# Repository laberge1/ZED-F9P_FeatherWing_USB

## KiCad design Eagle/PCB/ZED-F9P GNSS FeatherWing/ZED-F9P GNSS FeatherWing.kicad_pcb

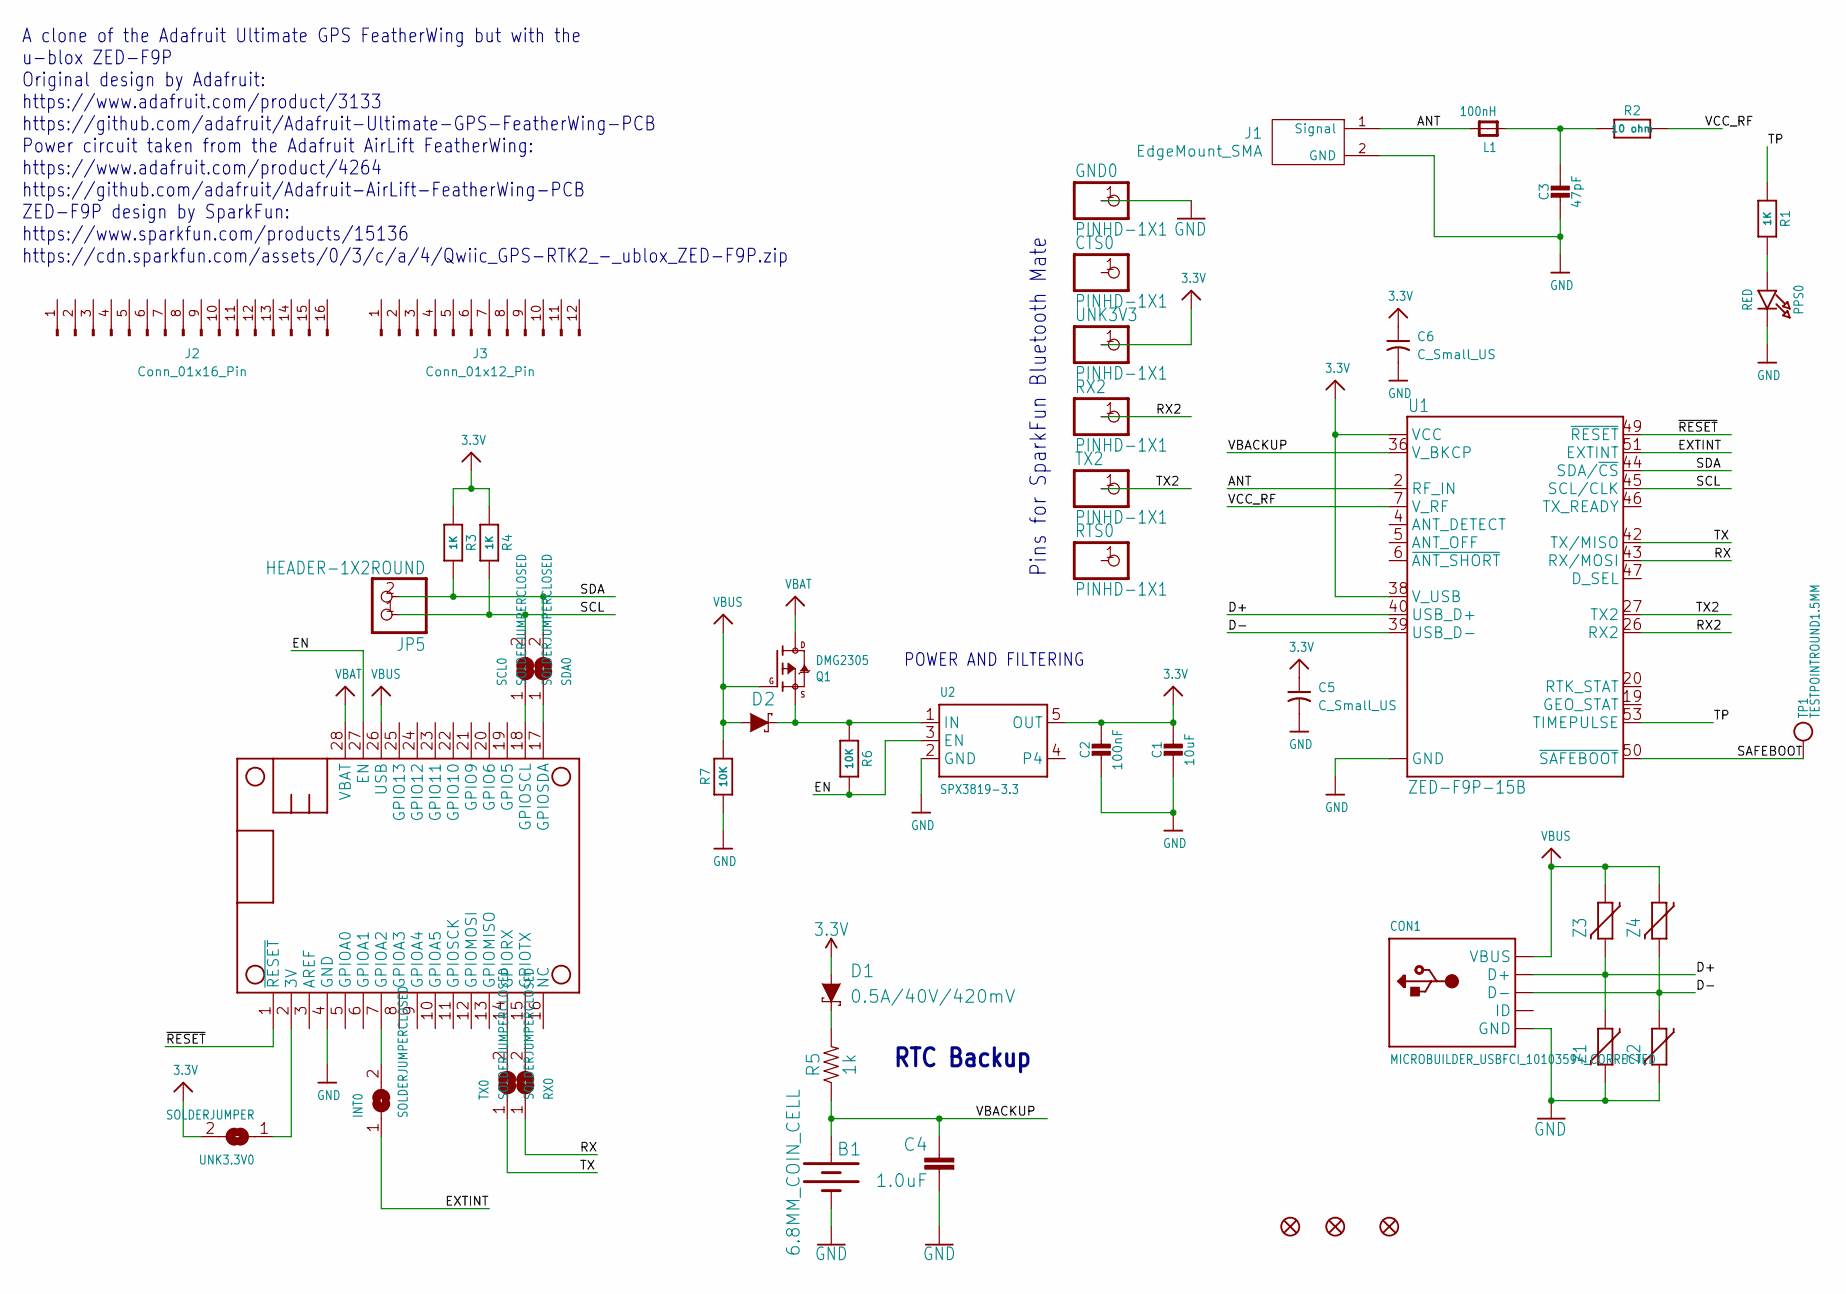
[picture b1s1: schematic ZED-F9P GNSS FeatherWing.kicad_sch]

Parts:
B1: 6.8MM_COIN_CELL; BATTCON-6.8MM; Digikey PN 728-1057-ND
C1: 10uF; 0805-NO; Voltage 6.3V; Digikey PN 1276-1298-1-ND
C2: 100nF; 0805-NO; Voltage 25V; Digikey PN 1276-2442-1-ND
C3: 47pF; C_0402_1005Metric; Digikey PN 490-14446-1-ND
C4: 1.0uF; 0603; Voltage 10V; Digikey PN 1276-1945-1-ND
C5, C6: C_Small_US; C_0402_1005Metric; Digikey PN 1276-1043-1-ND
CON1: MICROBUILDER_USBFCI_10103594_CORRECTED; MICROBUILDER_FCI_10103594_CORRECTED; Digikey PN 609-4050-1-ND
CTS0: PINHD-1X1; 1X01
D1, D2: 0.5A/40V/420mV; SOD-323; Digikey PN 1801-BAT201M3RRGCT-ND
FID1, FID2, FID3: FIDUCIAL""; Fiducial_0.5mm_Mask1mm
GND0: PINHD-1X1; 1X01
INT0: SOLDERJUMPERCLOSED; SolderJumper-2_P1.3mm_Bridged_RoundedPad1.0x1.5mm
J1: EdgeMount_SMA; SMA_Molex_0732512120; Digikey PN WM5536-ND
J2: Conn_01x16_Pin; Digikey PN 2223-SSK01-MPH-254-A16-ND
J3: Conn_01x12_Pin; Digikey PN 2223-SSK01-MPH-254-A12-ND
JP5: HEADER-1X2ROUND; 1X02_ROUND
L1: 100nH; L_0603_1608Metric; Digikey PN 490-15766-1-ND
MS1: MICROBUILDER_FEATHERWINGMICROBUILDER_FEATHERWING_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; MICROBUILDER_FEATHERWING_HOLES
PPS0: RED; CHIPLED_0805_NOOUTLINE; Digikey PN 732-4984-1-ND
Q1: DMG2305; SOT23-R; Digikey PN FDN340PCT-ND
R1, R3, R4: 1K; 0603-NO; Digikey PN 13-RT0603FRE131KLCT-ND
R2: 10 ohm; R_0402_1005Metric; Digikey PN CR0402-JW-100GLFCT-ND
R5: 1k; 0603; Digikey PN 13-RT0603FRE131KLCT-ND
R6, R7: 10K; 0603-NO; Digikey PN RNCP0603FTD10K0CT-ND
RTS0: PINHD-1X1; 1X01
RX0: SOLDERJUMPERCLOSED; SolderJumper-2_P1.3mm_Bridged_RoundedPad1.0x1.5mm
RX2: PINHD-1X1; 1X01
SCL0: SOLDERJUMPERCLOSED; SolderJumper-2_P1.3mm_Bridged_RoundedPad1.0x1.5mm
SDA0: SOLDERJUMPERCLOSED; SolderJumper-2_P1.3mm_Bridged_RoundedPad1.0x1.5mm
TP1: TESTPOINTROUND1.5MM; TESTPOINT_ROUND_1.5MM
TX0: SOLDERJUMPERCLOSED; SolderJumper-2_P1.3mm_Bridged_RoundedPad1.0x1.5mm
TX2: PINHD-1X1; 1X01
U1: ZED-F9P-15B; ZED-F9P_ZED-F9P; Digikey PN 672-ZED-F9P-15BCT-ND
U2: SPX3819-3.3; SOT23-5; Digikey PN 1016-1873-1-ND
UNK3.3V0: SOLDERJUMPER; SolderJumper-2_P1.3mm_Open_RoundedPad1.0x1.5mm
UNK3V3: PINHD-1X1; 1X01
Z1, Z2, Z3, Z4: CG0603MLC-05E; CT_CN0603; Digikey PN CG0603MLC-05ECT-ND

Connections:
3.3V: C1.1, C2.1, C5.1, C6.1, D1.A, R3.1, R4.1, U1.33 (VCC), U1.34 (VCC), U1.38 (V_USB), U2.5 (OUT), UNK3.3V0.2, UNK3V3.1 (1_1)
/ANT: J1.1 (Signal), L1.2, U1.2 (RF_IN)
/D+: CON1.D+, U1.40 (USB_D+), Z1.1, Z3.2
/D-: CON1.D-, U1.39 (USB_D-), Z2.1, Z4.2
/EN: MS1.27 (EN), R6.2, U2.3 (EN)
/EXTINT: INT0.1, U1.51 (EXTINT)
/RX: RX0.1, U1.43 (RX/MOSI)
/RX2: RX2.1 (1_1), U1.26 (RX2)
/SAFEBOOT: TP1.P$1 (P$1_P$1), U1.50 (~SAFEBOOT)
/SCL: JP5.1, R4.2, SCL0.2, U1.45 (SCL/CLK)
/SDA: JP5.2, R3.2, SDA0.2, U1.44 (SDA/~CS)
/TP: R1.1, U1.53 (TIMEPULSE)
/TX: TX0.1, U1.42 (TX/MISO)
/TX2: TX2.1 (1_1), U1.27 (TX2)
/VBACKUP: B1.+, C4.1, R5.1, U1.36 (V_BKCP)
/VCC_RF: R2.2, U1.7 (V_RF)
/~RESET: MS1.1 (~RESET), U1.49 (~RESET)
GND: B1.-, C1.2, C2.2, C3.2, C4.2, C5.2, C6.2, CON1.BASE@1 (GND), CON1.BASE@2 (GND), CON1.GND, CON1.SPRT@1 (GND), CON1.SPRT@2 (GND), CON1.SPRT@3 (GND), CON1.SPRT@4 (GND), GND0.1 (1_1), J1.2 (GND), MS1.4 (GND), PPS0.C, R7.1, U1.1 (GND), U1.3 (GND), U1.12 (GND), U1.14 (GND), U1.32 (GND), U1.37 (GND), U1.41 (GND), U1.48 (GND), U1.55 (GND), U1.56 (GND), U1.57 (GND), U1.58 (GND), U1.59 (GND), U1.60 (GND), U1.61 (GND), U1.62 (GND), U1.63 (GND), U1.64 (GND), U1.65 (GND), U1.66 (GND), U1.67 (GND), U1.68 (GND), U1.69 (GND), U1.70 (GND), U1.71 (GND), U1.72 (GND), U1.73 (GND), U1.74 (GND), U1.75 (GND), U1.76 (GND), U1.77 (GND), U1.78 (GND), U1.79 (GND), U1.80 (GND), U1.81 (GND), U1.82 (GND), U1.83 (GND), U1.84 (GND), U1.85 (GND), U1.86 (GND), U1.87 (GND), U1.88 (GND), U1.89 (GND), U1.90 (GND), U1.91 (GND), U1.92 (GND), U1.93 (GND), U1.94 (GND), U1.95 (GND), U1.96 (GND), U1.97 (GND), U1.98 (GND), U1.99 (GND), U1.100 (GND), U1.101 (GND), U1.102 (GND), U2.2 (GND), Z1.2, Z2.2
unnamed: D1.C, R5.2
unnamed: C3.1, L1.1, R2.1
unnamed: MS1.2 (3V), UNK3.3V0.1
unnamed: INT0.2, MS1.7 (GPIOA2)
unnamed: MS1.14 (GPIORX), TX0.2
unnamed: MS1.18 (GPIOSCL), SCL0.1
unnamed: MS1.17 (GPIOSDA), SDA0.1
unnamed: MS1.15 (GPIOTX), RX0.2
unnamed: PPS0.A, R1.2
unnamed: D2.C, Q1.2 (S), R6.1, U2.1 (IN)
VBAT: MS1.28 (VBAT), Q1.3 (D)
VBUS: CON1.VBUS, D2.A, MS1.26 (USB), Q1.1 (G), R7.2, Z3.1, Z4.1

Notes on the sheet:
POWER AND FILTERING
A clone of the Adafruit Ultimate GPS FeatherWing but with the u-blox ZED-F9P Original design by Adafruit: https://www.adafruit.com/product/3133 https://github.com/adafruit/Adafruit-Ultimate-GPS-FeatherWing-PCB Power circuit taken from the Adafruit AirLift FeatherWing: https://www.adafruit.com/produ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
RTC Backup
Pins for SparkFun Bluetooth Mate

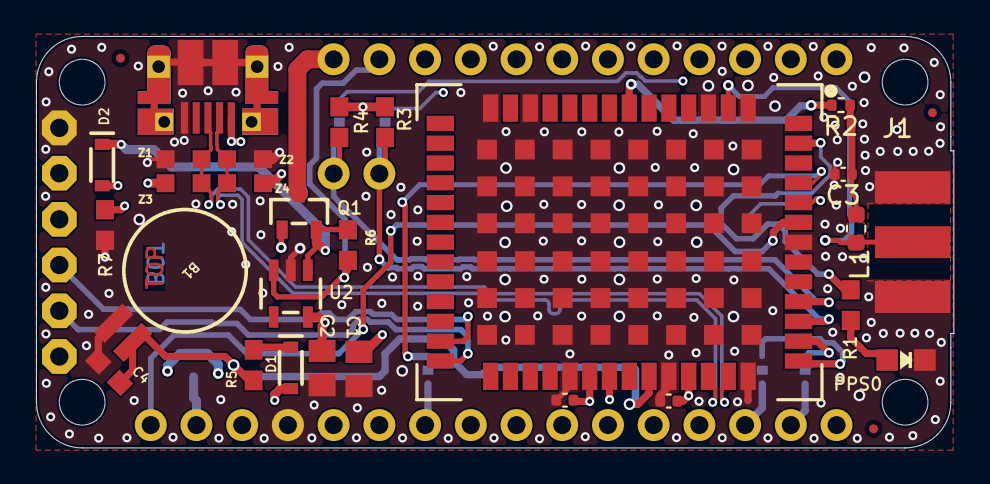
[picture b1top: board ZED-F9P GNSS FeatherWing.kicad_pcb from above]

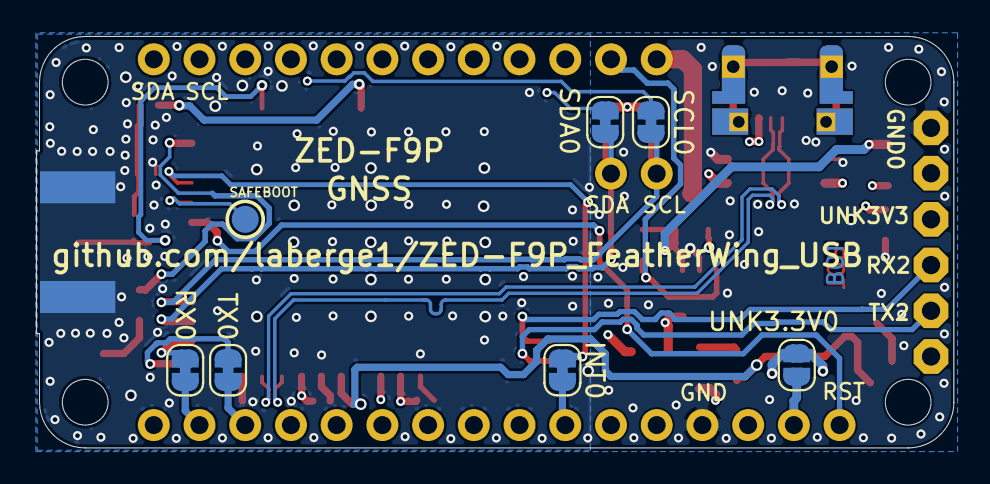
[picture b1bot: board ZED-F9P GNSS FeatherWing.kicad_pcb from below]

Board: 4 copper layers, 51.0 x 22.9 mm, 45 parts (13 on the bottom side), 30 nets.

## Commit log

2026-03-21 Translated to Kicad
2026-03-23 Minor updates
2026-05-29 Update to Kicad 10 and added SMA
2026-06-07 V2 Release
    Released to fab.
